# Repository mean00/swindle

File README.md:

<picture>
  <source media="(prefers-color-scheme: dark)" srcset="assets/web/swindle_logo3.png">
  
</picture>

<h1 align="center">🔧 SWINDLE — ARM / RISC-V Debug Probe</h1>

<p align="center">
  <b>Turn any cheap dev board into a full-featured debug probe.</b>
</p>

<blockquote>
  <strong>TL;DR</strong> — Got an RP2040 board lying around? You've got a debug probe.<br>
  Swindle is a <strong>multi-platform debug probe</strong> for embedded devices, supporting <strong>SWD</strong> (ARM Cortex-M) and <strong>RVSWD</strong> (RISC-V CH32V2xx/CH32V3xx). It's powered by the incredible <a href="https://black-magic.org/index.html">Black Magic Probe</a> engine with a custom Rust-based GDB interface.
</blockquote>

---

## ✨ Features

| Category | Details |
|----------|---------|
| **🧠 Engine** | Built on top of the proven [Black Magic Probe](https://black-magic.org/index.html) firmware engine |
| **🦀 GDB Interface** | Written in **Rust** — modern, safe, and maintainable |
| **🔌 Protocols** | SWD (ARM) + RVSWD (RISC-V) — no JTAG |
| **🎯 Breakpoints** | Infinite breakpoints in RAM (ARM/RV32) + soft flash breakpoints for targets without HW breakpoints (some WCH chips) |
| **📡 RTOS Support** | **FreeRTOS** awareness and **SEGGER RTT** out of the box — no configuration needed |
| **💾 DFU Update** | Firmware updates over USB DFU — no programmer required |
| **📺 RTT Channel** | Dedicated USB Tx only RTT channel (RP2xxx & CH32V3xx) |
| **🌐 Networking** | Experimental networked version based on **CH32V307** or RP2040+W5500 (DHCP + port 2000/20001) |
| **🔋 Low Cost** | RP2040-Zero boards are dirt cheap! |
| **🔧 Voltage Translation** | Optional custom PCB with voltage level translators |

---

## 🧩 Supported Hardware

### Probe Hosts (runs Swindle)

You need **≥256 KB flash** and **≥48 KB RAM**.

| Platform | Status | Notes |
|----------|--------|-------|
| **RP2040** (e.g. RP2040-Zero) | ✅ Stable | The most affordable option |
| **RP2350** (e.g. RP2350-Zero) | 🧪 Experimental | |
| **GD32F303CCT6** (48/64-pin) | ✅ Stable | |
| **CH32V30xxx** | ✅ Stable | RISC-V based host |
| **Custom PCB** | 🧩 Optional | With voltage translators, mosfet on reset, ws2812 |

### Debug Targets

| Architecture | Protocol | Device Families |
|-------------|----------|-----------------|
| **ARM Cortex-M** | SWD | RP2040, RP2350, STM32, GD32, and many ARM Cortex-M with SWD |
| **RISC-V** | RVSWD | WCH CH32V2xx, CH32V3xx |

---

## 🚀 Getting Started

### 1. Flash the firmware

Pick the pre-built firmware for your board or [build from source](#-building).

> **Flashing via DFU (RP2040):** Hold `BOOTSEL`, plug in USB, then copy the `.uf2` file.

### 2. Connect to your target

```
Probe SWDIO  →  Target SWDIO
Probe SWCLK  →  Target SWCLK
Probe GND    →  Target GND
Probe NRST   →  Target NRST   (optional, recommended)
Probe TX     →  Target Uart TX    (optional)
```

'see wiki for exact pinout'
### 3. Start debugging

```bash
# Connect with GDB
gdb-multiarch -ex "target extended-remote /dev/ttyACM0" -ex "mon swdp_scan" -ex "attach 1" your_firmware.elf
```

Or use any GDB frontend (VS Code, CLion, etc.) — just point it to the serial port.

---

## 🔨 Building

This project uses **CMake** with presets for each target platform.

There is a devpod/docker build environment included.

### Prerequisites

- CMake ≥ 3.21
- ARM GCC toolchain (`arm-none-eabi-gcc`) or LLVM/Clang
- RISC-V toolchain (for CH32V targets)
- Rust toolchain (for the GDB interface)

### Configure & Build

```bash
# Configure for your target
cmake --preset rp2040          # RP2040-Zero
cmake --preset rp2350          # RP2350-Zero
cmake --preset gd32f303_48     # GD32F303 48-pin
cmake --preset gd32f303_64     # GD32F303 64-pin
cmake --preset ch32v307        # CH32V307 (networked)

# Build
cmake --build --preset rp2040
```

> **Note:** Some presets have variants with inverted NRST (`*_inv`), with WS2812 RGB led.
> See `CMakePresets.json` for the full list.

| Preset | Description |
|--------|-------------|
| `rp2040` | RP2040-Zero (USB) |
| `rp2040_inv` | RP2040-Zero with inverted NRST |
| `rp2350` | RP2350-Zero (USB, experimental) |
| `gd32f303_48` | GD32F303 48-pin (USB) |
| `gd32f303_64` | GD32F303 64-pin (USB) |
| `gd32f303_48_inv_ws2812` | GD32F303 48-pin (USB) +WS2812 +inv RST |
| `gd32f303_64_inv_ws2812` | GD32F303 64-pin (USB) +WS2812 +inv RST |
| `ch32v307` | CH32V30x (USB) |
| `ch32v307_inv_ws2812` | CH32V30x (USB) +ws2812 + inv RST|
| `ch32v307_net` | CH32V307 (Ethernet, experimental) |
| `rp2040_zero_w5500` | rp2040+w5500 (Ethernet, experimental) |

---

## 📘 Documentation

Full documentation is available on the **[Swindle Wiki](https://github.com/mean00/swindle/wiki)** — covering:

- 🔧 Hardware setup and wiring guides
- 🖥️ GDB integration and troubleshooting
- ⚙️ Advanced configuration
- 🧪 RTOS-aware debugging
- 🌐 Networked probe setup

---

## 🏗️ Project Architecture

```
swindle/                    # Debug probe wrapper
├── rs/                     # Rust GDB interface (rs_swindle / rsbmp)
│   ├── rs_swindle/         # Core GDB logic
│   └── rs_swindle_wrapper/ # C → Rust bridge
└── swindle/                # C++ Black Magic Probe engine + wrapper

esprit/                     # C++ / Rust SDK framework (HAL + RTOS + MCU drivers)

assets/                     # Images and media
cmake/                      # Project-level CMake utilities
```

---

## 🖼️ Gallery

| Small probe, big target | RP2040 + CH32V |
|:------------------------:|:--------------:|
|  |  |
|:------------------------:|:--------------:|

---

---

## 🤝 Contributing

Contributions, issues, and feature requests are welcome!
Feel free to check the [issues page](https://github.com/mean00/swindle/issues).

---

## 📄 License

This project is built on the [Black Magic Probe](https://black-magic.org/index.html) engine, licensed under **GPL-3.0**.

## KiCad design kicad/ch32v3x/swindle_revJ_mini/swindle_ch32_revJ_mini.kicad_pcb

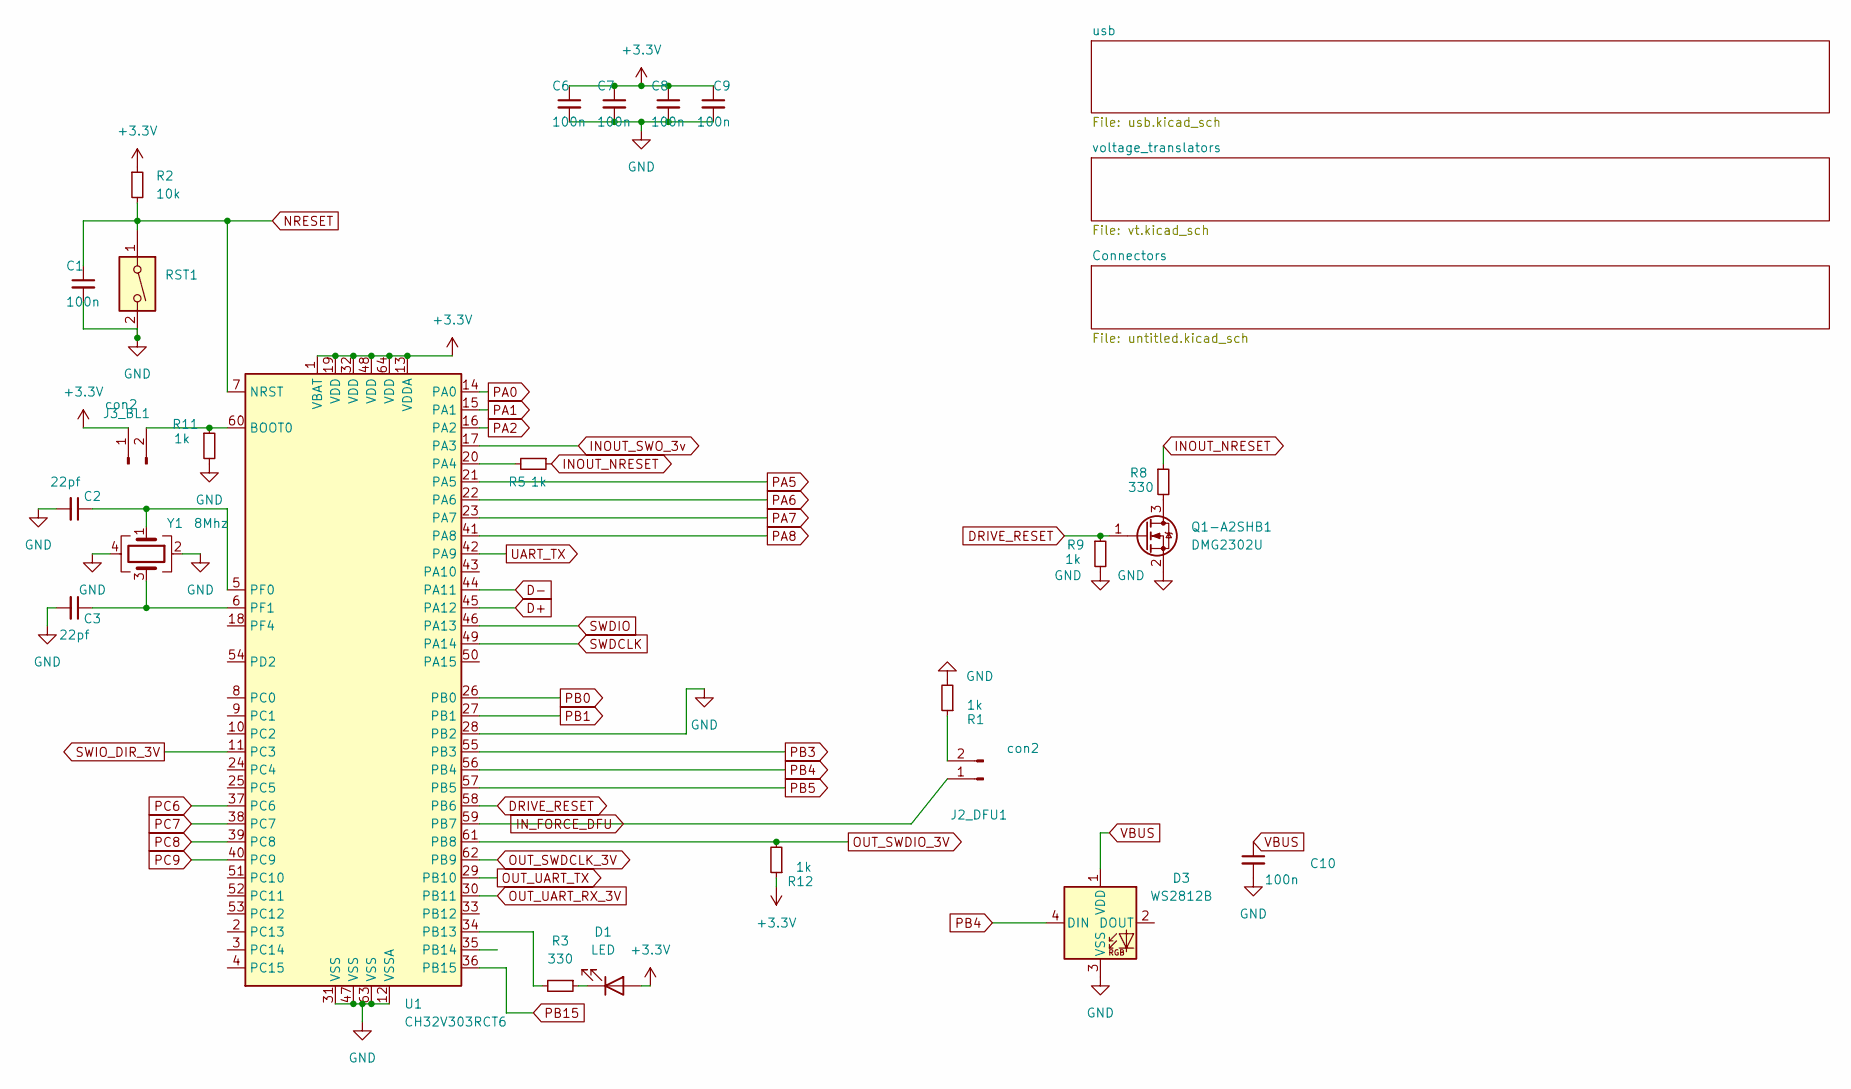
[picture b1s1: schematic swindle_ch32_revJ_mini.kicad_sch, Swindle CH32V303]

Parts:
C1, C6, C7, C8, C9, C10: 100n; R_0603_1608Metric
C2, C3: 22pf; R_0603_1608Metric
D1: LED; D_0805_2012Metric
D3: WS2812B; LED_WS2812B_PLCC4_5.0x5.0mm_P3.2mm
J2_DFU1, J3_BL1: con2; PinHeader_1x02_P1.27mm_Vertical
Q1-A2SHB1: DMG2302U; SOT-23
R1, R5, R9, R11, R12: 1k; R_0603_1608Metric
R2: 10k; R_0603_1608Metric
R3, R8: 330; R_0603_1608Metric
RST1: SW_DIP_x01; SW_SPST_CK_RS282G05A3
U1: CH32V303RCT6; LQFP-64_10x10mm_P0.5mm
Y1: 8Mhz; Crystal_SMD_TXC_7M-4Pin_3.2x2.5mm_45deg

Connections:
+3.3V: C6.1, C7.1, C8.1, C9.1, D1.2 (A), J3_BL1.1, R2.1, R12.1, U1.1 (VBAT), U1.13 (VDDA), U1.19 (VDD), U1.32 (VDD), U1.48 (VDD), U1.64 (VDD); also elsewhere on the board
D+: U1.45 (PA12); also elsewhere on the board
D-: U1.44 (PA11); also elsewhere on the board
DRIVE_RESET: Q1-A2SHB1.1 (G), R9.1, U1.58 (PB6)
GND: C1.2, C2.2, C3.2, C6.2, C7.2, C8.2, C9.2, C10.2, D3.3 (VSS), Q1-A2SHB1.2 (S), R1.2, R9.2, R11.2, RST1.2, U1.12 (VSSA), U1.28 (PB2), U1.31 (VSS), U1.47 (VSS), U1.63 (VSS), Y1.2, Y1.4; also elsewhere on the board
INOUT_NRESET: R5.1, R8.1; also elsewhere on the board
INOUT_SWO: U1.17 (PA3)
IN_FORCE_DFU: J2_DFU1.1, U1.59 (PB7)
NRESET: C1.1, R2.2, RST1.1, U1.7 (NRST); also elsewhere on the board
unnamed: D1.1 (K), R3.1
unnamed: J2_DFU1.2, R1.1
unnamed: J3_BL1.2, R11.1, U1.60 (BOOT0)
unnamed: Q1-A2SHB1.3 (D), R8.2
unnamed: R5.2, U1.20 (PA4)
unnamed: R3.2, U1.34 (PB13)
unnamed: C2.1, U1.5 (PF0), Y1.1
unnamed: C3.1, U1.6 (PF1), Y1.3
OUT_UART_TX: U1.29 (PB10)
PA0: U1.14 (PA0); also elsewhere on the board
PA1: U1.15 (PA1); also elsewhere on the board
PA2: U1.16 (PA2); also elsewhere on the board
PA5: U1.21 (PA5); also elsewhere on the board
PA6: U1.22 (PA6); also elsewhere on the board
PA7: U1.23 (PA7); also elsewhere on the board
PA8: U1.41 (PA8)
PB0: U1.26 (PB0); also elsewhere on the board
PB1: U1.27 (PB1); also elsewhere on the board
PB3: U1.55 (PB3)
PB4: D3.4 (DIN), U1.56 (PB4)
PB5: U1.57 (PB5)
PB15: U1.36 (PB15); also elsewhere on the board
PC6: U1.37 (PC6); also elsewhere on the board
PC7: U1.38 (PC7); also elsewhere on the board
PC8: U1.39 (PC8); also elsewhere on the board
PC9: U1.40 (PC9); also elsewhere on the board
SWDCLK: U1.49 (PA14); also elsewhere on the board
SWDIO: U1.46 (PA13); also elsewhere on the board
SWIO_DIR_3V: U1.11 (PC3)
UART_TX: U1.42 (PA9); also elsewhere on the board
VBUS: C10.1, D3.1 (VDD); also elsewhere on the board

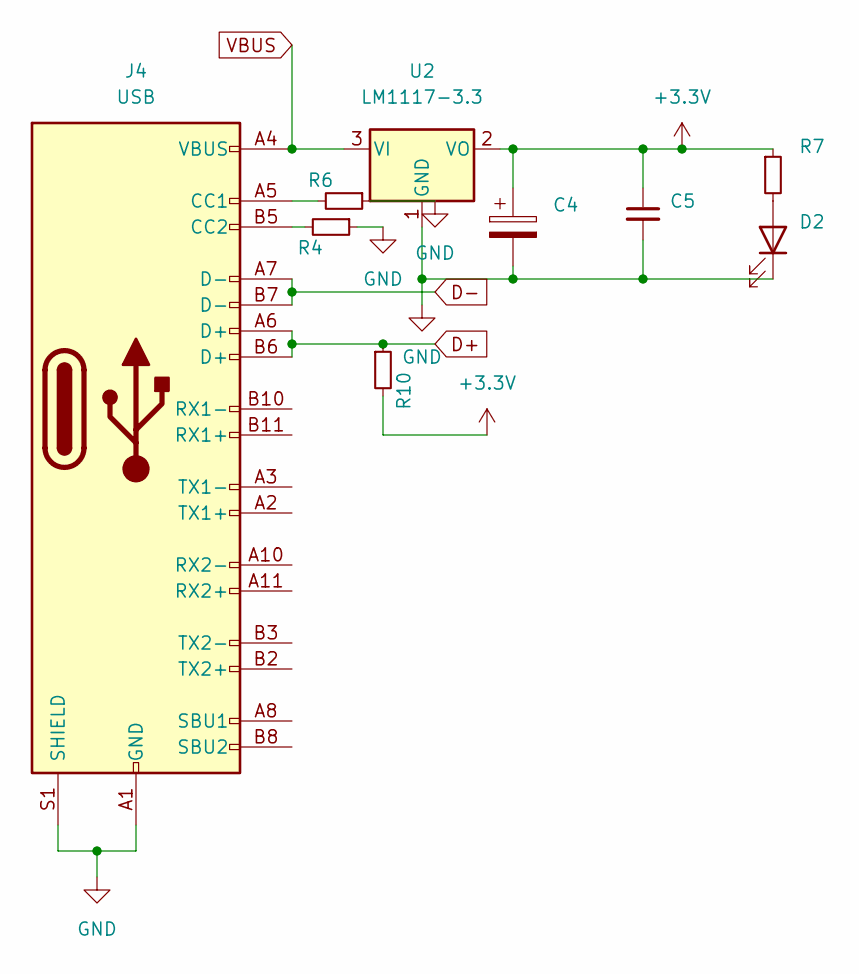
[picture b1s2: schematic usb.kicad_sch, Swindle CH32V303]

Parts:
C4: 100u; C_1206_3216Metric_Pad1.33x1.80mm_HandSolder
C5: 100n; R_0603_1608Metric
D2: LED; D_0805_2012Metric
J4: USB; USB_C_Receptacle_Palconn_UTC16-G
R4, R6: 5.1k; R_0603_1608Metric
R7: 330; R_0603_1608Metric
R10: 1.2k; R_0603_1608Metric
U2: LM1117-3.3; SOT-223

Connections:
+3.3V: C4.1, C5.1, R7.1, R10.2, U2.2 (VO); also elsewhere on the board
D+: J4.A6 (D+), J4.B6 (D+), R10.1; also elsewhere on the board
D-: J4.A7 (D-), J4.B7 (D-); also elsewhere on the board
GND: C4.2, C5.2, D2.1 (K), J4.A1 (GND), J4.A12 (GND), J4.B1 (GND), J4.B12 (GND), J4.S1 (SHIELD), R4.1, R6.1, U2.1 (GND); also elsewhere on the board
unnamed: D2.2 (A), R7.2
unnamed: J4.A5 (CC1), R6.2
unnamed: J4.B5 (CC2), R4.2
VBUS: J4.A4 (VBUS), J4.A9 (VBUS), J4.B4 (VBUS), J4.B9 (VBUS), U2.3 (VI); also elsewhere on the board

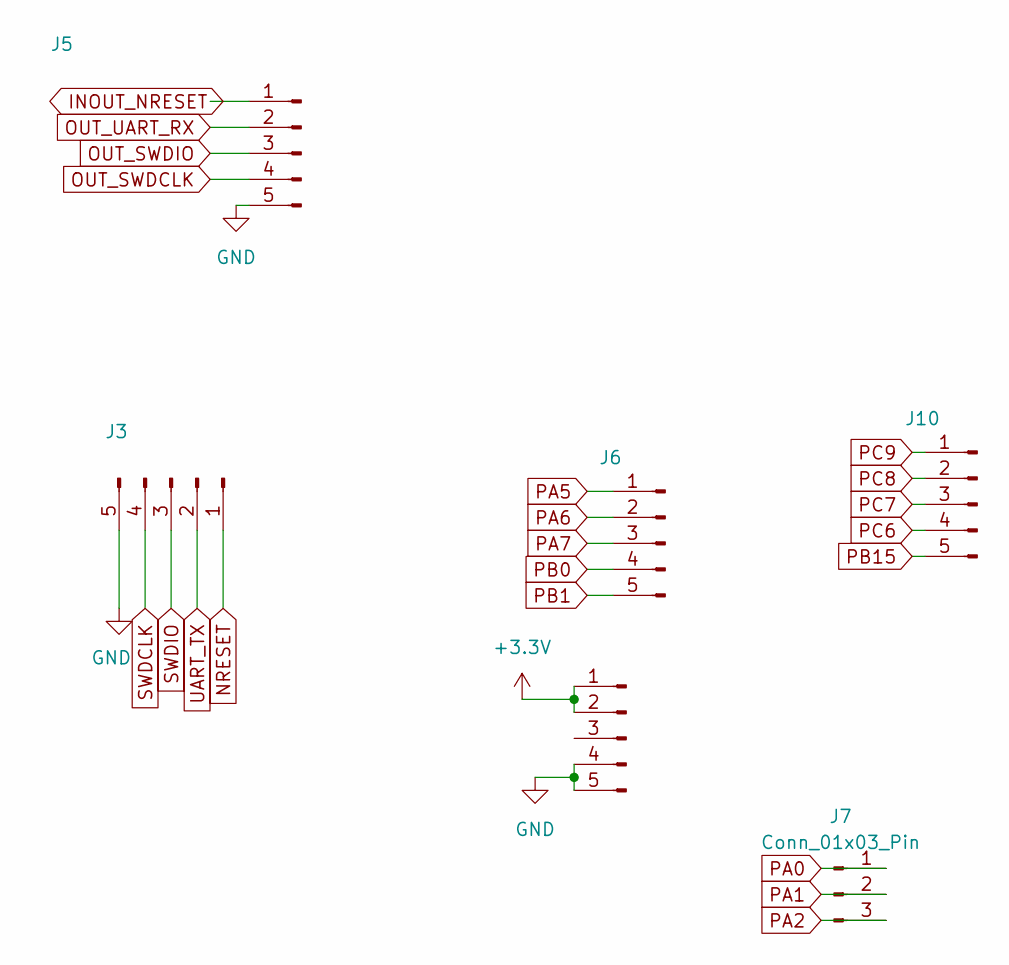
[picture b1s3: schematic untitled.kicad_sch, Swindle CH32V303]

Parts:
J3: Dbg; PinSocket_1x05_P1.27mm_Vertical
J5: Debug port; JST_XH_B5B-XH-A_1x05_P2.50mm_Vertical
J6, J8, J10: Debug port; PinSocket_1x05_P1.27mm_Vertical
J7: Conn_01x03_Pin; PinSocket_1x03_P1.27mm_Vertical

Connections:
+3.3V: J8.1, J8.2; also elsewhere on the board
GND: J3.5, J5.5, J8.4, J8.5; also elsewhere on the board
INOUT_NRESET: J5.1; also elsewhere on the board
NRESET: J3.1; also elsewhere on the board
PA0: J7.1; also elsewhere on the board
PA1: J7.2; also elsewhere on the board
PA2: J7.3; also elsewhere on the board
PA5: J6.1; also elsewhere on the board
PA6: J6.2; also elsewhere on the board
PA7: J6.3; also elsewhere on the board
PB0: J6.4; also elsewhere on the board
PB1: J6.5; also elsewhere on the board
PB15: J10.5; also elsewhere on the board
PC6: J10.4; also elsewhere on the board
PC7: J10.3; also elsewhere on the board
PC8: J10.2; also elsewhere on the board
PC9: J10.1; also elsewhere on the board
SWDCLK: J3.4; also elsewhere on the board
SWDIO: J3.3; also elsewhere on the board
UART_TX: J3.2; also elsewhere on the board

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
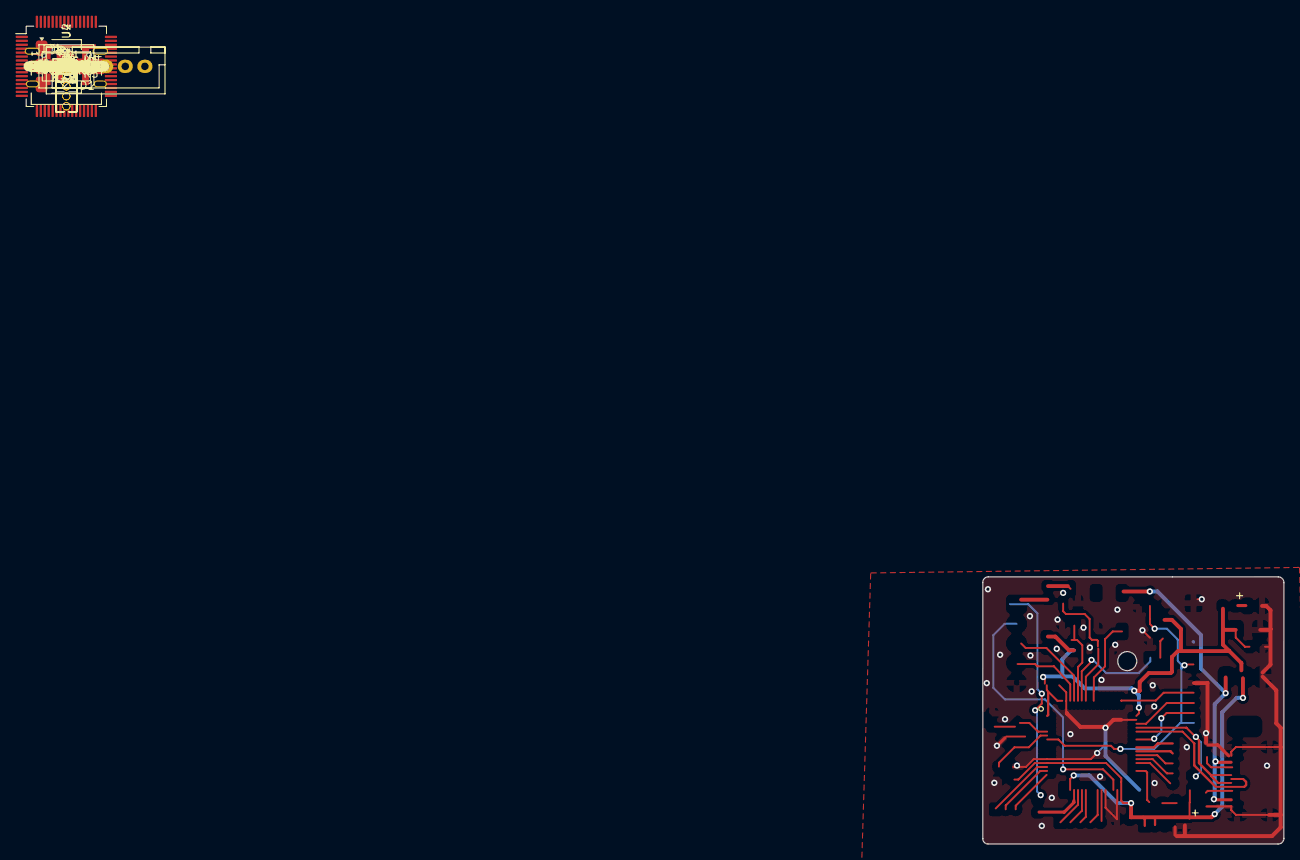
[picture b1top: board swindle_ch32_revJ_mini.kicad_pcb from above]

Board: 2 copper layers, 38.3 x 34.0 mm, 57 parts (0 on the bottom side), 40 nets.

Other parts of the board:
kibuzzard-6A634FB9: G***; kibuzzard-6A634FB9
kibuzzard-6A635004: G***; kibuzzard-6A635004
kibuzzard-6A635025: G***; kibuzzard-6A635025
kibuzzard-6A635259: G***; kibuzzard-6A635259
kibuzzard-6AB8B403: G***; kibuzzard-6AB8B403
kibuzzard-65C1C8EE, kibuzzard-65C1C8EE#2: G***; kibuzzard-65C1C8EE
kibuzzard-65C1C9D7: G***; kibuzzard-65C1C9D7
kibuzzard-65C1C92F: G***; kibuzzard-65C1C92F
kibuzzard-65C1C789, kibuzzard-65C1C789#2: G***; kibuzzard-65C1C789
kibuzzard-65C1C918: G***; kibuzzard-65C1C918
kibuzzard-65C1C972: G***; kibuzzard-65C1C972
kibuzzard-6714FD4B: G***; kibuzzard-6714FD4B
kibuzzard-67135D9A: G***; kibuzzard-67135D9A
kibuzzard-67135D50: G***; kibuzzard-67135D50
kibuzzard-671361D3: G***; kibuzzard-671361D3
kibuzzard-68694355: G***; kibuzzard-68694355

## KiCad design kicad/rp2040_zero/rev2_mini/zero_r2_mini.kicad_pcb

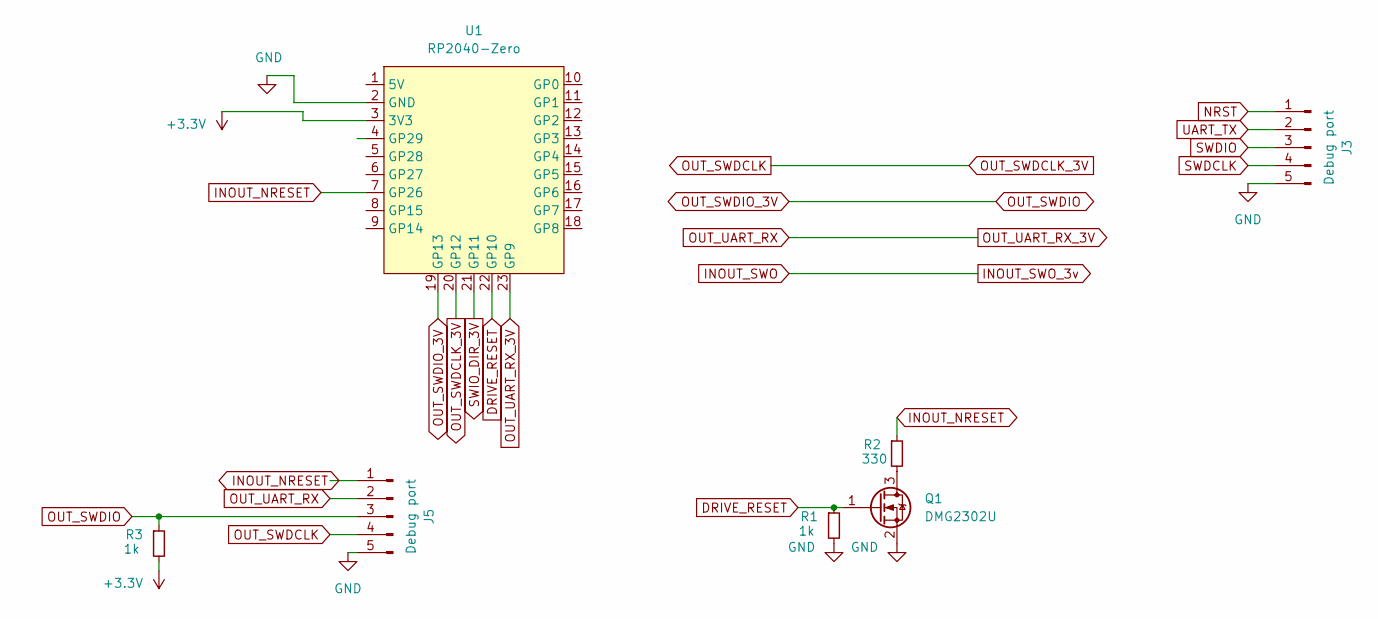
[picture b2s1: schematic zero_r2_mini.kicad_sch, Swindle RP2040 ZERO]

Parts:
J3: Debug port; PinHeader_1x05_P1.27mm_Vertical
J5: Debug port; Con5
Q1: DMG2302U; SOT-23
R1, R3: 1k; R_0603_1608Metric
R2: 330; R_0603_1608Metric
U1: RP2040-Zero; RP2040 Zero

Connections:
+3.3V: R3.2, U1.3 (3V3); also elsewhere on the board
DRIVE_RESET: Q1.1 (G), R1.1, U1.22 (GP10)
GND: J3.5, J5.5, Q1.2 (S), R1.2, U1.2 (GND); also elsewhere on the board
INOUT_NRESET: J5.1, R2.1, U1.7 (GP26)
NRST: J3.1
unnamed: Q1.3 (D), R2.2
OUT_SWDCLK: J5.4, U1.20 (GP12)
OUT_SWDIO: J5.3, R3.1, U1.19 (GP13)
OUT_UART_RX: J5.2, U1.23 (GP9)
SWDCLK: J3.4
SWDIO: J3.3
SWIO_DIR_3V: U1.21 (GP11)
UART_TX: J3.2

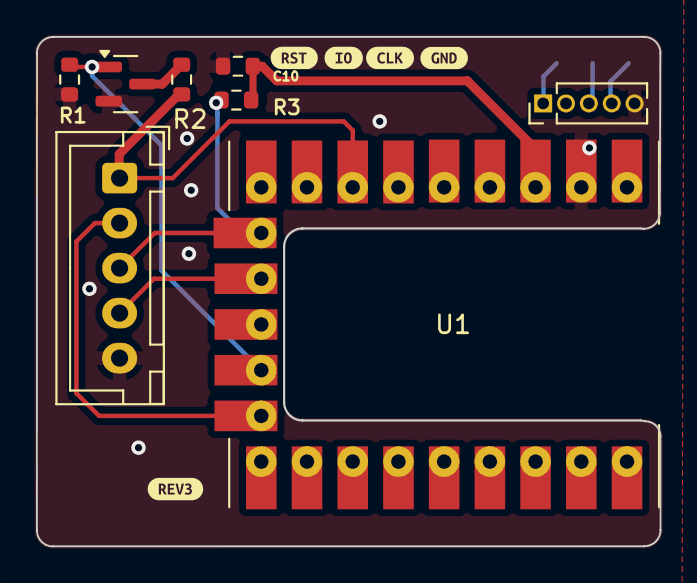
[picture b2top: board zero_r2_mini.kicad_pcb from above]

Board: 2 copper layers, 34.6 x 28.3 mm, 13 parts (0 on the bottom side), 8 nets.

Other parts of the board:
C10: 100n; R_0603_1608Metric
kibuzzard-6AAE3AD3: G***; kibuzzard-6AAE3AD3
kibuzzard-67D71CE3: G***; kibuzzard-67D71CE3
kibuzzard-67D71D2A: G***; kibuzzard-67D71D2A
kibuzzard-67D71D3A: G***; kibuzzard-67D71D3A
kibuzzard-67D71D53: G***; kibuzzard-67D71D53

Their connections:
+3.3V: C10.1; also elsewhere on the board
GND: C10.2; also elsewhere on the board

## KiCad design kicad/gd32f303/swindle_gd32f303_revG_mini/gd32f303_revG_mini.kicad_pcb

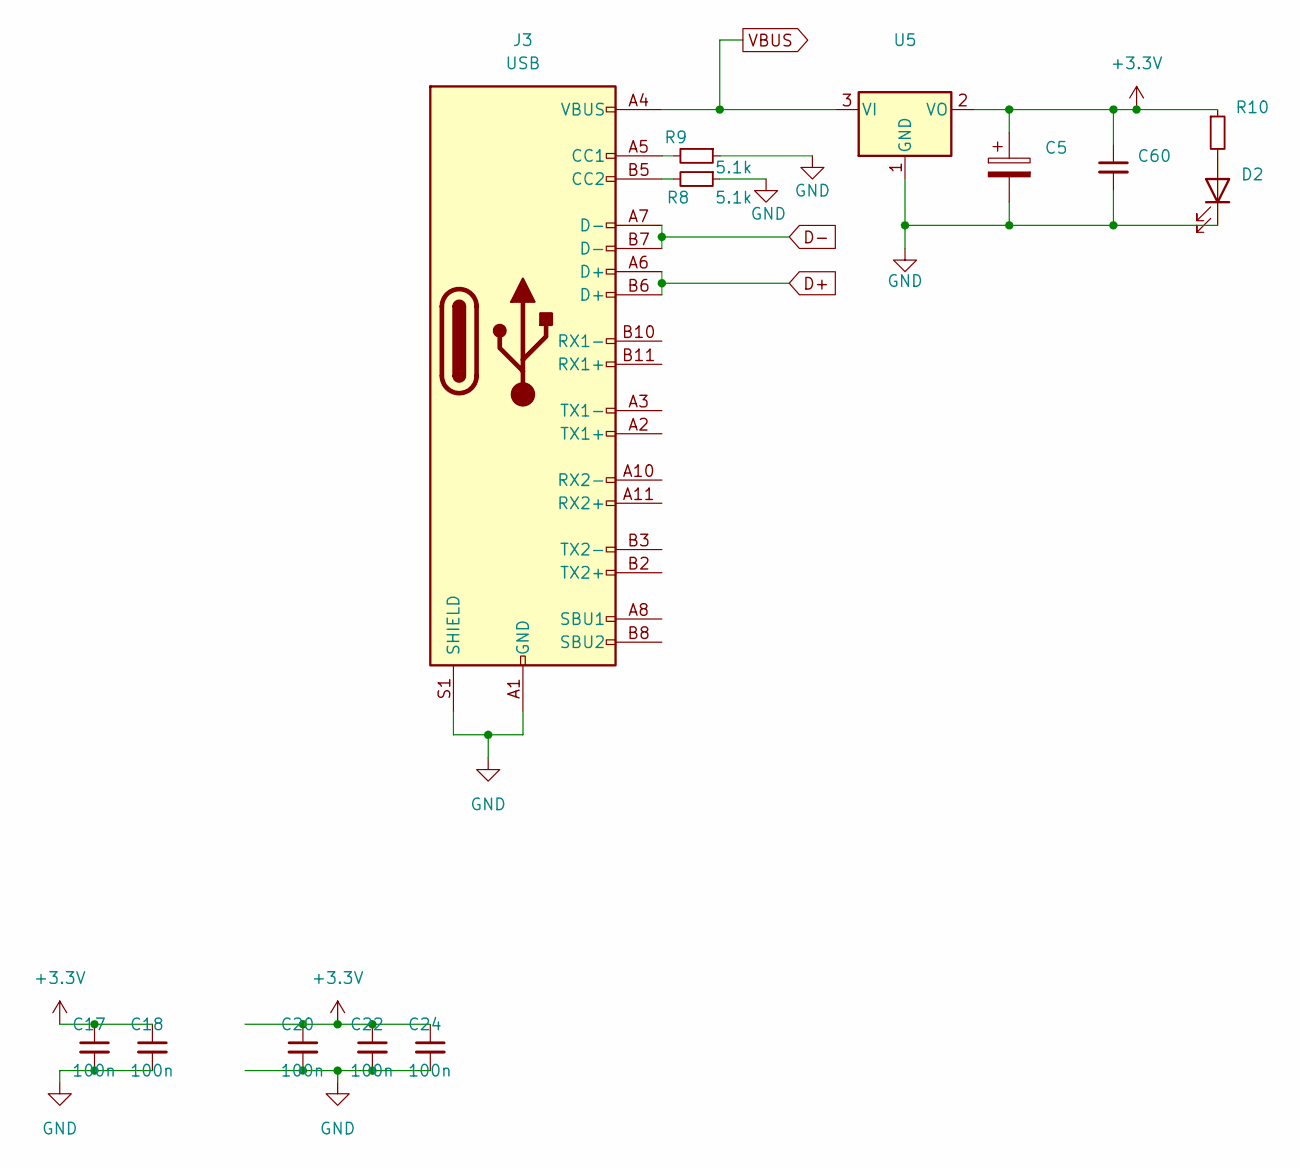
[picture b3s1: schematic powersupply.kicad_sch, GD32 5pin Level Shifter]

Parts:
C5: 100u; C_1206_3216Metric_Pad1.33x1.80mm_HandSolder
C17, C18, C20, C22, C24, C60: 100n; R_0603_1608Metric
D2: LED; D_0805_2012Metric
J3: USB; USB_C_Receptacle_Palconn_UTC16-G_no_hole
R8, R9: 5.1k; R_0603_1608Metric
R10: 330; R_0603_1608Metric
U5: LM1117-3.3; SOT-223

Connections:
+3.3V: C5.1, C17.1, C18.1, C20.1, C22.1, C24.1, C60.1, R10.1, U5.2 (VO); also elsewhere on the board
D+: J3.A6 (D+), J3.B6 (D+); also elsewhere on the board
D-: J3.A7 (D-), J3.B7 (D-); also elsewhere on the board
GND: C5.2, C17.2, C18.2, C20.2, C22.2, C24.2, C60.2, D2.1 (K), J3.A1 (GND), J3.A12 (GND), J3.B1 (GND), J3.B12 (GND), J3.S1 (SHIELD), R8.1, R9.1, U5.1 (GND); also elsewhere on the board
unnamed: D2.2 (A), R10.2
unnamed: J3.A5 (CC1), R9.2
unnamed: J3.B5 (CC2), R8.2
VBUS: J3.A4 (VBUS), J3.A9 (VBUS), J3.B4 (VBUS), J3.B9 (VBUS), U5.3 (VI); also elsewhere on the board

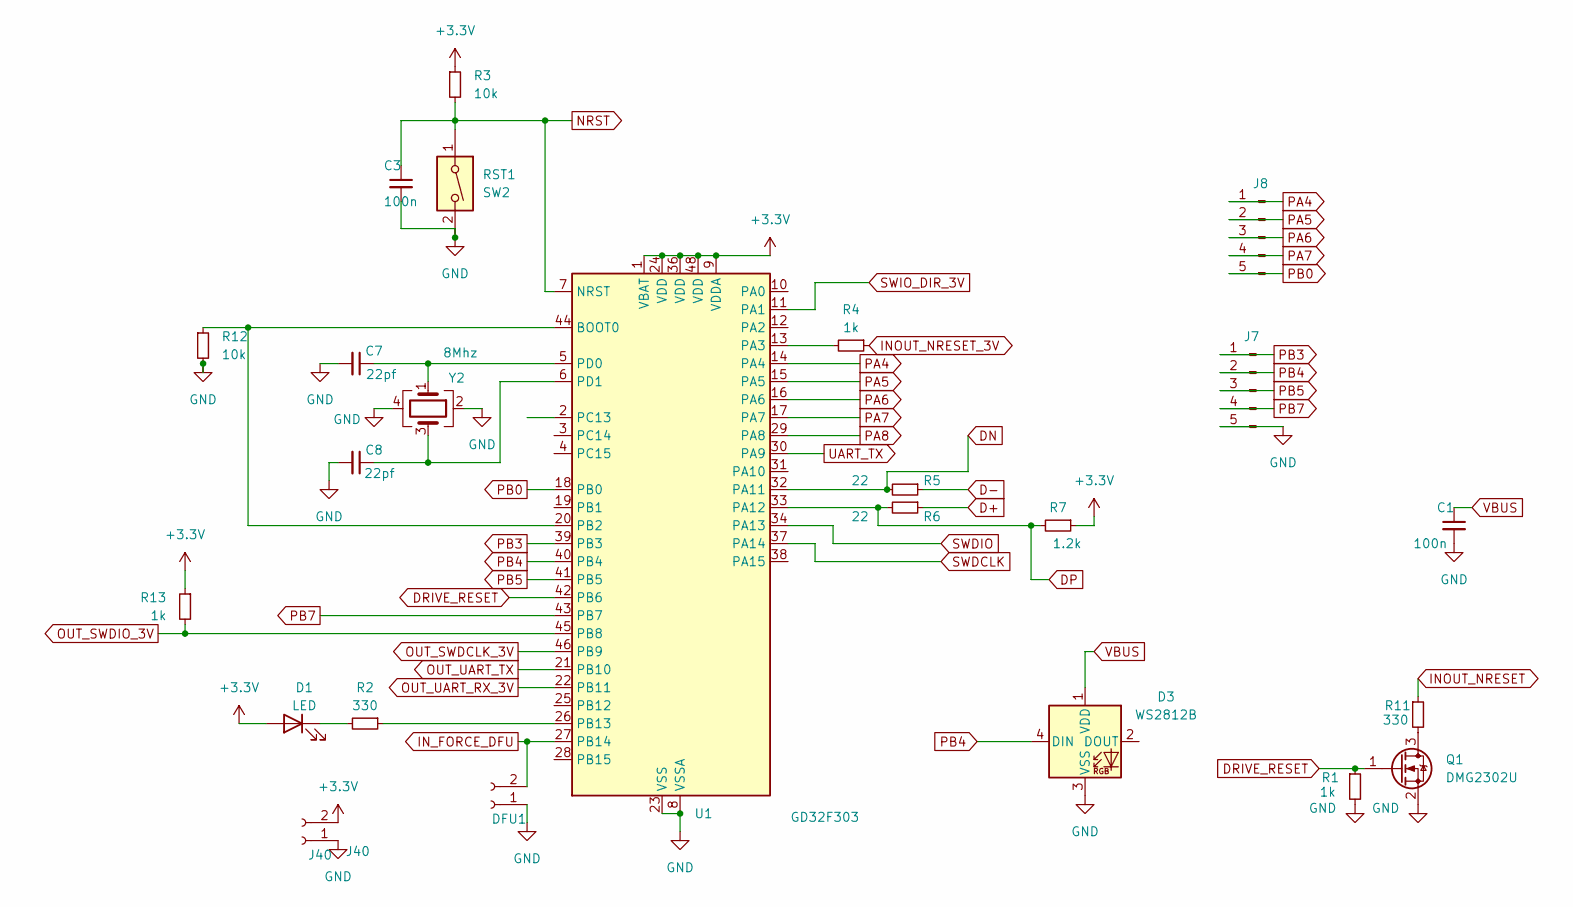
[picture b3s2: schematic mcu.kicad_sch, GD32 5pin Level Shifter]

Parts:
C1, C3: 100n; R_0603_1608Metric
C7, C8: 22pf; R_0603_1608Metric
D1: LED; D_0805_2012Metric
D3: WS2812B; LED_WS2812B_PLCC4_5.0x5.0mm_P3.2mm
DFU1: DFU; PinHeader_1x02_P1.27mm_Vertical
J7: Conn_01x05_Pin; PinSocket_1x05_P1.27mm_Vertical
J8: PinSocket_1x05_P1.27mm_Vertical
J40: J40; PinHeader_1x02_P1.27mm_Vertical
Q1: DMG2302U; SOT-23
R1, R4, R13: 1k; R_0603_1608Metric
R2, R11: 330; R_0603_1608Metric
R3, R12: 10k; R_0603_1608Metric
R5, R6: 22; R_0603_1608Metric
R7: 1.2k; R_0603_1608Metric
RST1: SW2; SW_SPST_CK_RS282G05A3
U1: GD32F303; LQFP-48_7x7mm_P0.5mm
Y2: 8Mhz; Crystal_SMD_TXC_7M-4Pin_3.2x2.5mm

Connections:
+3.3V: D1.2 (A), J40.2, R3.1, R7.1, R13.1, U1.1 (VBAT), U1.9 (VDDA), U1.24 (VDD), U1.36 (VDD), U1.48 (VDD); also elsewhere on the board
D+: R6.1; also elsewhere on the board
D-: R5.1; also elsewhere on the board
DN: R5.2, U1.32 (PA11)
DP: R6.2, R7.2, U1.33 (PA12)
DRIVE_RESET: Q1.1 (G), R1.1, U1.42 (PB6)
GND: C1.2, C3.2, C7.2, C8.2, D3.3 (VSS), DFU1.1, J7.5, J40.1, Q1.2 (S), R1.2, R12.2, RST1.2, U1.8 (VSSA), U1.23 (VSS), U1.35 (VSS), U1.47 (VSS), Y2.2, Y2.4; also elsewhere on the board
INOUT_NRESET: R4.1, R11.1; also elsewhere on the board
IN_FORCE_DFU: DFU1.2, U1.27 (PB14)
NRST: C3.1, R3.2, RST1.1, U1.7 (NRST); also elsewhere on the board
unnamed: D1.1 (K), R2.2
unnamed: Q1.3 (D), R11.2
unnamed: R12.1, U1.20 (PB2), U1.44 (BOOT0)
unnamed: R4.2, U1.13 (PA3)
unnamed: R2.1, U1.26 (PB13)
unnamed: C7.1, U1.5 (PD0), Y2.1
unnamed: C8.1, U1.6 (PD1), Y2.3
OUT_SWDCLK_3V: U1.46 (PB9); also elsewhere on the board
OUT_SWDIO_3V: R13.2, U1.45 (PB8); also elsewhere on the board
OUT_UART_RX_3V: U1.22 (PB11); also elsewhere on the board
OUT_UART_TX: U1.21 (PB10)
PA4: J8.1, U1.14 (PA4)
PA5: J8.2, U1.15 (PA5)
PA6: J8.3, U1.16 (PA6)
PA7: J8.4, U1.17 (PA7)
PA8: U1.29 (PA8)
PB0: J8.5, U1.18 (PB0)
PB3: J7.1, U1.39 (PB3)
PB4: D3.4 (DIN), J7.2, U1.40 (PB4)
PB5: J7.3, U1.41 (PB5)
PB7: J7.4, U1.43 (PB7)
SWDCLK: U1.37 (PA14); also elsewhere on the board
SWDIO: U1.34 (PA13); also elsewhere on the board
SWIO_DIR_3V: U1.11 (PA1)
UART_TX: U1.30 (PA9); also elsewhere on the board
VBUS: C1.1, D3.1 (VDD); also elsewhere on the board

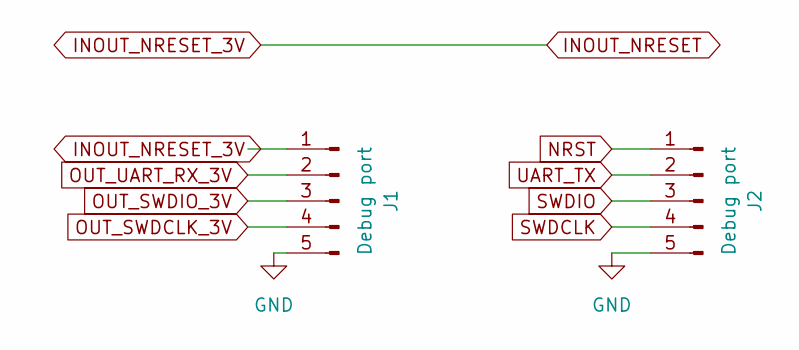
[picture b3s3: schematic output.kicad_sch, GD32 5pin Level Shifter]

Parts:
J1: Debug port; JST_XH_B5B-XH-A_1x05_P2.50mm_Vertical
J2: Debug port; PinSocket_1x05_P1.27mm_Vertical

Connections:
GND: J1.5, J2.5; also elsewhere on the board
INOUT_NRESET: J1.1; also elsewhere on the board
NRST: J2.1; also elsewhere on the board
OUT_SWDCLK_3V: J1.4; also elsewhere on the board
OUT_SWDIO_3V: J1.3; also elsewhere on the board
OUT_UART_RX_3V: J1.2; also elsewhere on the board
SWDCLK: J2.4; also elsewhere on the board
SWDIO: J2.3; also elsewhere on the board
UART_TX: J2.2; also elsewhere on the board

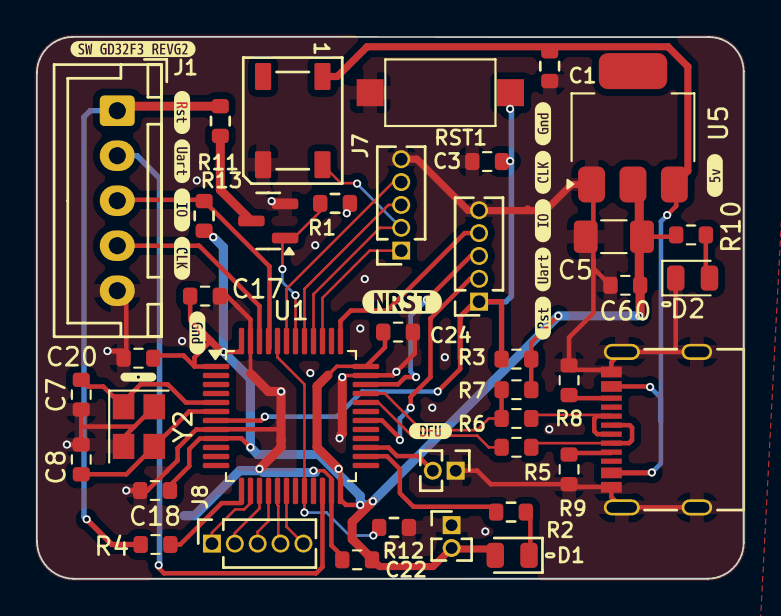
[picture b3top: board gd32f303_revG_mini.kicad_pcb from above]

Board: 2 copper layers, 39.3 x 30.1 mm, 56 parts (0 on the bottom side), 36 nets.

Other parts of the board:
kibuzzard-68AB27BD: G***; kibuzzard-68AB27BD
kibuzzard-683DFE0C, kibuzzard-683DFE0C#2: G***; kibuzzard-683DFE0C
kibuzzard-68610AC9: G***; kibuzzard-68610AC9
kibuzzard-672226BD: G***; kibuzzard-672226BD
kibuzzard-672281C9, kibuzzard-672281C9#2: G***; kibuzzard-672281C9
kibuzzard-672281D4, kibuzzard-672281D4#2: G***; kibuzzard-672281D4
kibuzzard-672281DC, kibuzzard-672281DC#2: G***; kibuzzard-672281DC
kibuzzard-672281E9, kibuzzard-672281E9#2: G***; kibuzzard-672281E9
kibuzzard-6722820B, kibuzzard-6722820B#2: G***; kibuzzard-6722820B
kibuzzard-6722831C: G***; kibuzzard-6722831C
kibuzzard-67228234: G***; kibuzzard-67228234

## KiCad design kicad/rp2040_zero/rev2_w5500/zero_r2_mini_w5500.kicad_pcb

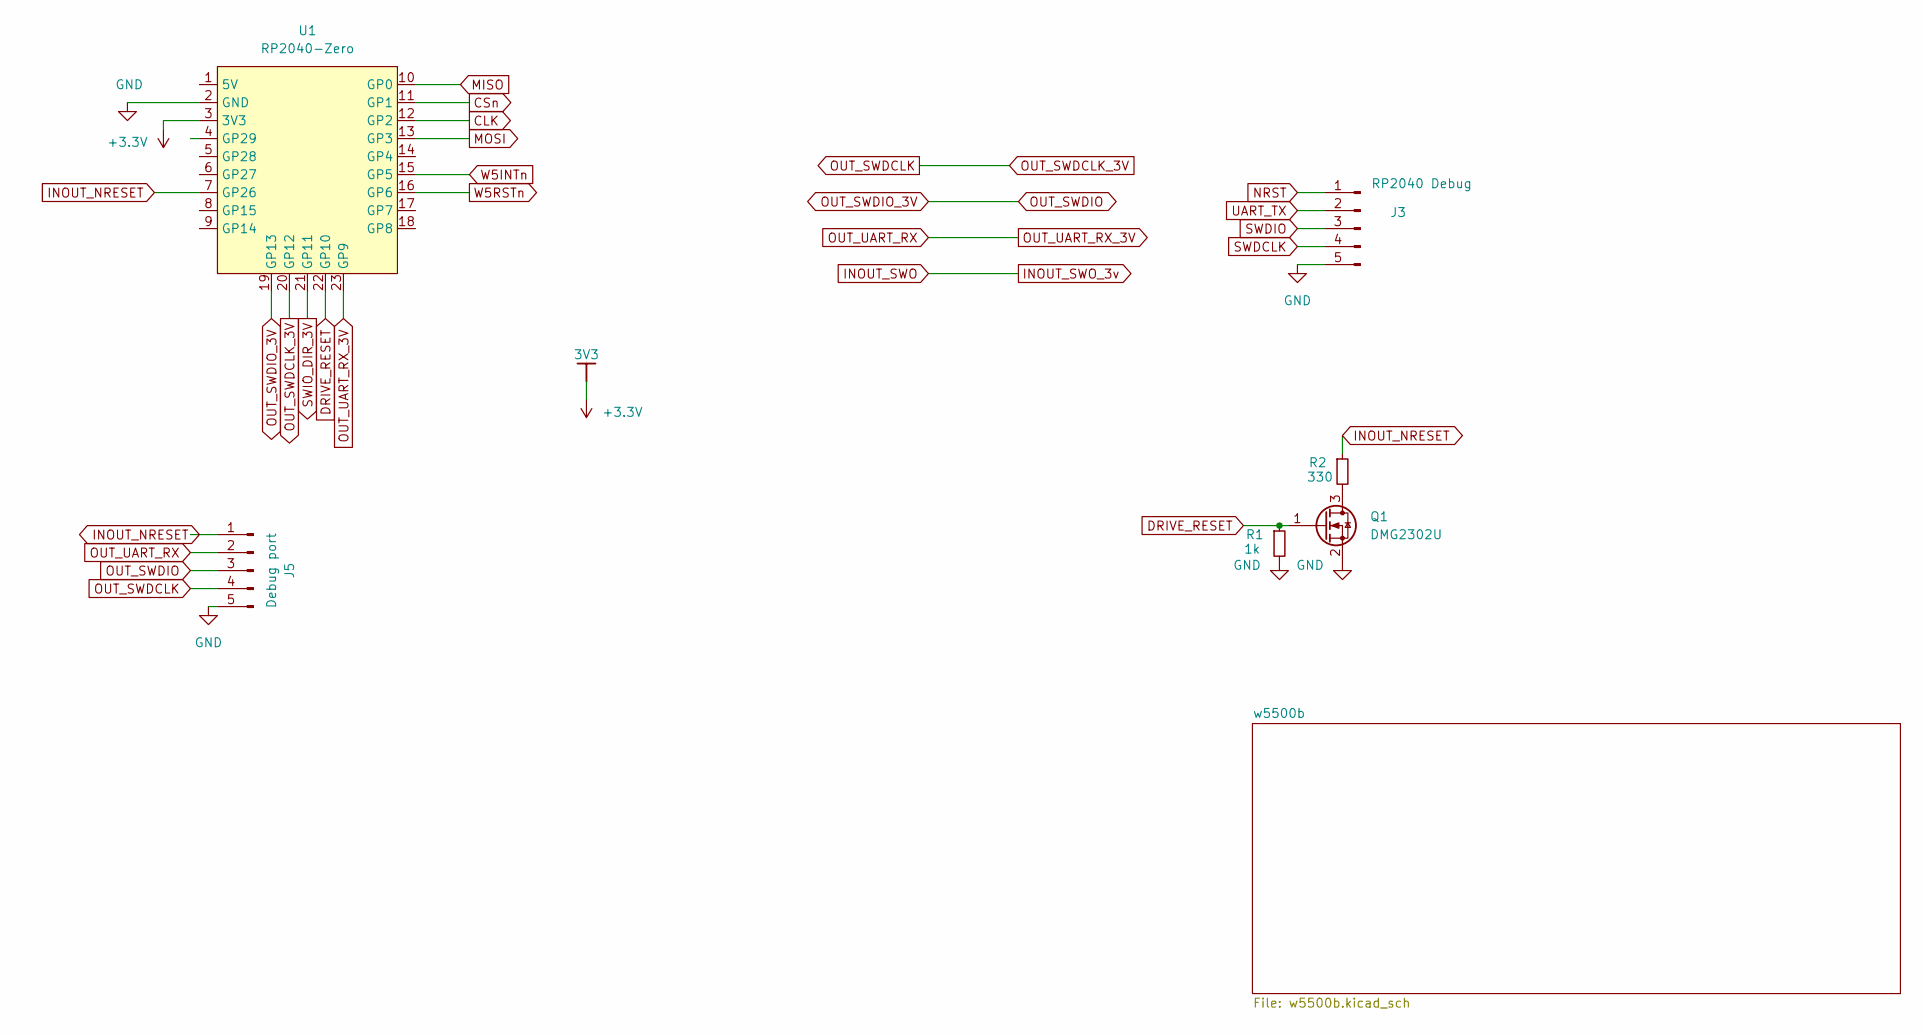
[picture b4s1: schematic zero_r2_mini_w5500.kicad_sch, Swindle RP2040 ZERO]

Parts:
J3: RP2040 Debug; PinHeader_1x05_P1.27mm_Vertical
J5: Debug port; Con5
Q1: DMG2302U; SOT-23
R1: 1k; R_0603_1608Metric
R2: 330; R_0603_1608Metric
U1: RP2040-Zero; RP2040 Zero

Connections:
+3.3V: U1.3 (3V3); also elsewhere on the board
CLK: U1.12 (GP2); also elsewhere on the board
CSn: U1.11 (GP1); also elsewhere on the board
DRIVE_RESET: Q1.1 (G), R1.1, U1.22 (GP10)
GND: J3.5, J5.5, Q1.2 (S), R1.2, U1.2 (GND); also elsewhere on the board
INOUT_NRESET: J5.1, R2.1, U1.7 (GP26)
MISO: U1.10 (GP0); also elsewhere on the board
MOSI: U1.13 (GP3); also elsewhere on the board
NRST: J3.1
unnamed: Q1.3 (D), R2.2
OUT_SWDCLK: J5.4, U1.20 (GP12)
OUT_SWDIO: J5.3, U1.19 (GP13)
OUT_UART_RX: J5.2, U1.23 (GP9)
SWDCLK: J3.4
SWDIO: J3.3
SWIO_DIR_3V: U1.21 (GP11)
UART_TX: J3.2
W5INTn: U1.15 (GP5); also elsewhere on the board
W5RSTn: U1.16 (GP6); also elsewhere on the board
